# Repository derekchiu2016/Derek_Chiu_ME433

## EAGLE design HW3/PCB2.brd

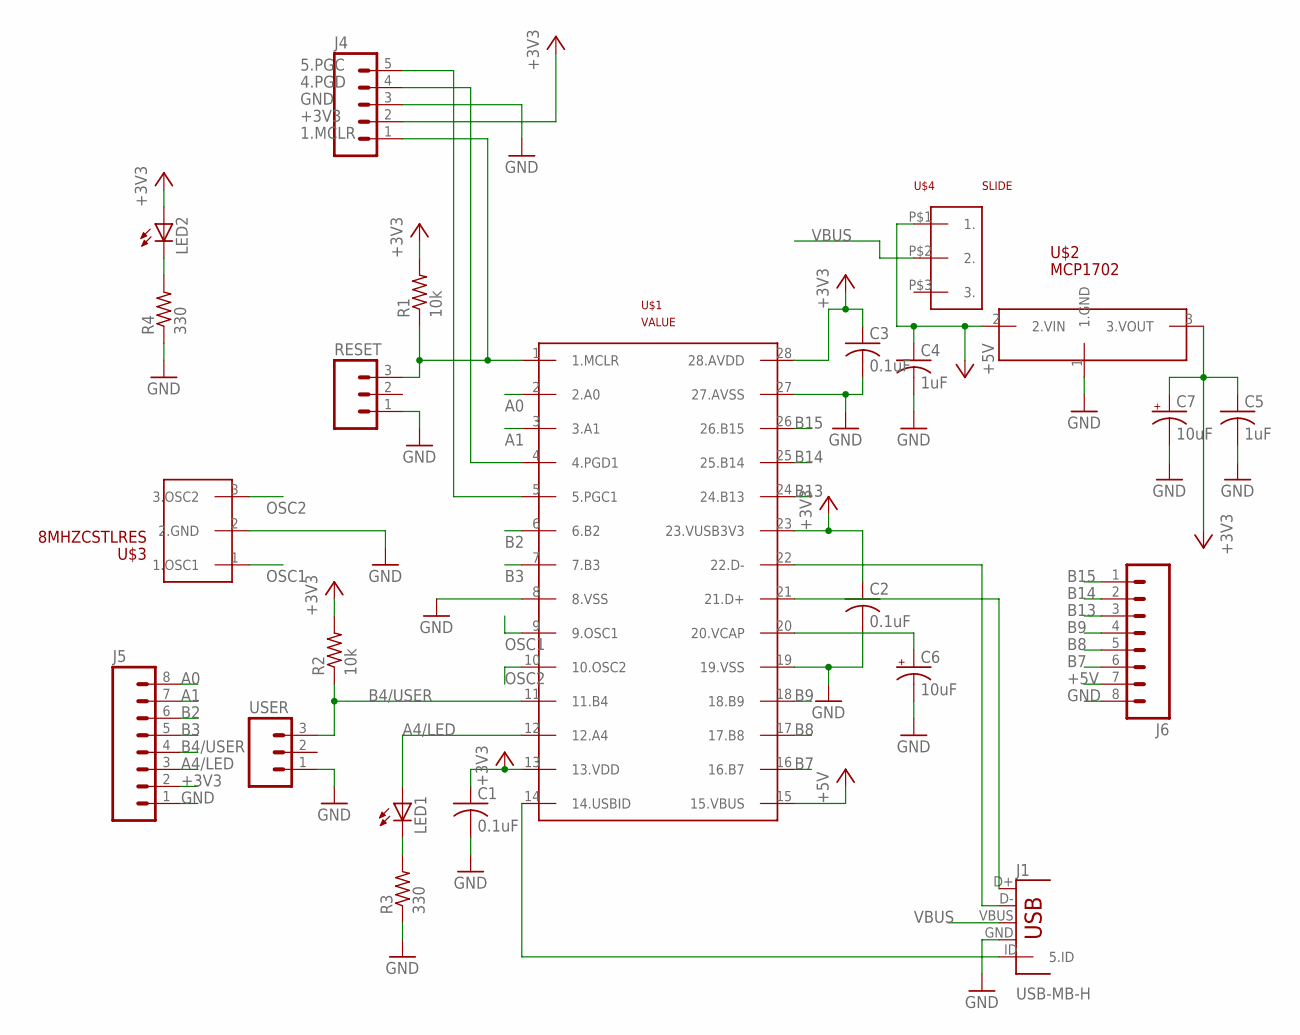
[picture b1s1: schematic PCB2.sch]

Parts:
C1, C2, C3: 0.1uF; C025-024X044
C4, C5: 1uF; C050-024X044
C6, C7: 10uF; TAP5-50
J1: USB-MB-H
J4: M05PTH; 1X05
J5, J6: M08; 1X08_ROUND
LED1, LED2: LED3MM
R1, R2: 10k; 0207/10
R3, R4: 330; 0207/10
RESET: M03PTH; 1X03
U$1: PIC32MX250F128B; DIL28-3
U$2: MCP1702; TO92
U$3: 8MHZCSTLRES; 1X03
U$4: SLIDE
USER: M03PTH; 1X03

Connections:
1.MCLR: J4.1, R1.1, RESET.3, U$1.1 (1.MCLR)
4.PGD: J4.4, U$1.4 (4.PGD1)
5.PGC: J4.5, U$1.5 (5.PGC1)
+3V3: C1.1, C2.1, C3.1, C5.1, C7.+, J4.2, J5.2, LED2.A, R1.2, R2.2, U$1.13 (13.VDD), U$1.23 (23.VUSB3V3), U$1.28 (28.AVDD), U$2.3 (3.VOUT)
+5V: C4.1, J6.7, U$1.15 (15.VBUS), U$2.2 (2.VIN), U$4.P$1 (1.)
A0: J5.8, U$1.2 (2.A0)
A1: J5.7, U$1.3 (3.A1)
A4/LED: J5.3, LED1.A, U$1.12 (12.A4)
B2: J5.6, U$1.6 (6.B2)
B3: J5.5, U$1.7 (7.B3)
B4/USER: J5.4, R2.1, U$1.11 (11.B4), USER.3
B7: J6.6, U$1.16 (16.B7)
B8: J6.5, U$1.17 (17.B8)
B9: J6.4, U$1.18 (18.B9)
B13: J6.3, U$1.24 (24.B13)
B14: J6.2, U$1.25 (25.B14)
B15: J6.1, U$1.26 (26.B15)
GND: C1.2, C2.2, C3.2, C4.2, C5.2, C6.-, C7.-, J1.GND, J4.3, J5.1, J6.8, R3.1, R4.1, RESET.1, U$1.8 (8.VSS), U$1.19 (19.VSS), U$1.27 (27.AVSS), U$2.1 (1.GND), U$3.2 (2.GND), USER.1
unnamed: LED1.K (C), R3.2
unnamed: J1.ID (5.ID), U$1.14 (14.USBID)
unnamed: J1.D-, U$1.22 (22.D-)
unnamed: J1.D+, U$1.21 (21.D+)
unnamed: C6.+, U$1.20 (20.VCAP)
unnamed: LED2.K (C), R4.2
OSC1: U$1.9 (9.OSC1), U$3.1 (1.OSC1)
OSC2: U$1.10 (10.OSC2), U$3.3 (3.OSC2)
VBUS: J1.VBUS, U$4.P$2 (2.)

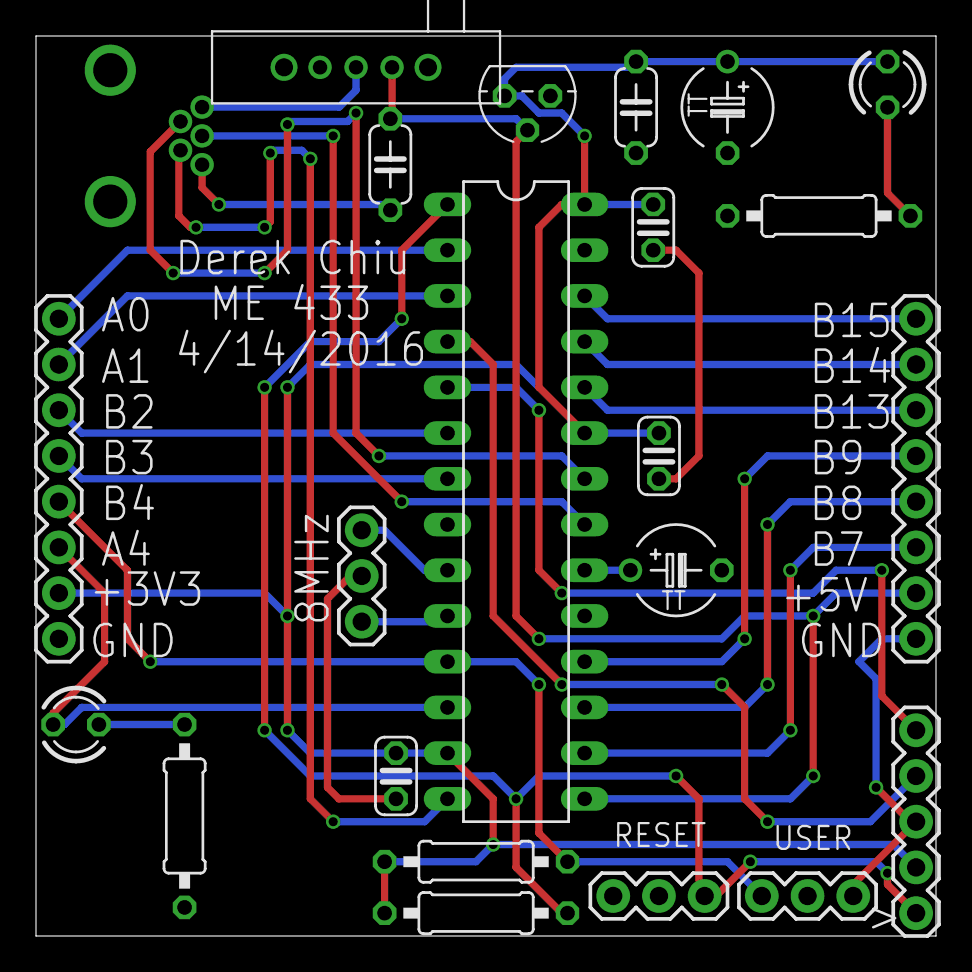
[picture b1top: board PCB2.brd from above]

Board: 2 copper layers, 50.0 x 50.0 mm, 23 parts (0 on the bottom side), 27 nets.

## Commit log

2016-03-31 :confetti_ball: Added .gitattributes & .gitignore files
2016-03-31 My first commit!
2016-03-31 Extra line added to change something
2016-04-02 Circuit pics, 3.3V oscill SShot, DEVCFG pragmas
    Added 2 pics of circuit
    Added screenshot of 3.3V oscillations due to no capacitors
    First edit of code filling out all DEVCFG registers
2016-04-04 Created new HW1 folder, same code
2016-04-04 PICkit3 working, initialized RB4 and RA4, LED from RA4 now ON
2016-04-04 Make LED turn ON/OFF every 5ms
    Using:
    _CP0_SET_COUNT
    _CP0_GET_COUNT
    LATAbits.LATA4
2016-04-04 Added code that turns off LED when pushbutton is pushed
    Using
    PORTBbits.RB4 to read pushbutton
    LATAbits.LATA4
2016-04-13 PCB Files
    Ready to be checked before order.
    NOTE: For some reason Eagle decided to lock my .sch and .brd files. Not
    exactly sure what it does, but just a heads up.
2016-04-13 Deleted HW2 folder
2016-04-16 Starting homework 4 code
    Copy and pasted sample SPI code from git
2016-04-16 For SPI: Added pin functions, added spi_io to setVoltage function
    Still need to figure out where pin functions go in the code.
    Still need to figure out how to fill out the rest of the DAC bits
2016-04-18 Finished setting up the spi_io function
    spi_io function now takes channel and voltage inputs and sends it to the
    SPI
    Next need to create the loops for the sine and triangle wave values
2016-04-18 setVoltage function complete
    Need to initiate and implement loops for sine wave and triangle wave
2016-04-19 Created sine and triangle waves
    Note: waves do not run exactly at 10 Hz
    Finished SPI DAC, time to start on I2C
2016-04-20 Copy and pasted i2c functions and changed all i2c1 to i2c2
2016-04-20 Set up initExpander, setExpander, and getExpander functions
    Next, need to incorporate inputs of setExpander into actual function
2016-04-20 Finished I2C initialization, need to work on set and getExpander functions
2016-04-21 Almost done, need to fix getExpander
2016-04-21 End HW4
    But double check getExpander function
2016-04-21 Fixed getExpander and finally added function prototypes
    problem was change char getExpander from void getExpander
2016-04-23 Create HW6, make sure IMU connections and I2C code works using WHOAMI reg
2016-04-23 Initialized IMU (3 registers), still missing some
    Initialized Accel, Gyro, and multi-read, but need to fill in some bits
    (x filter, etc.)
2016-04-23 Started i2c_read_multiple function
    Next, need to make sure addresses and stuff work
2016-04-24 Started PWM setup
    Need to correct the frequency, next need to change duty cycle depending
    on accelerations
2016-04-25 Finished setup of PWM
    f = 10kHz, duty cycle = 50%
2016-04-25 Solved i2c_read_multiple, set up 50Hz reading frequency
    Need to POWER CYCLE each time you upload code
2016-04-25 Set the sampling frequency to 50Hz and scale duty cycles depending on a_X and a_Y
2016-04-25 Minor edit
2016-05-06 Started HW5 (moving in all functions and library)
    Also contains minor edits to IMU hw/IMU tests
2016-05-06 completed drawCharacter function
    writes a single character at some coordinate
2016-05-06 uses LCD_drawArray to print Hello World! 1337
2016-05-07 Added pictures of Hello World 1337 and IMU reading
2016-05-13 Got IMU working
    Also uploaded new picture
2016-05-13 Added comments
2016-05-15 Android Hello World App
2016-05-30 Added laser cut box stuff
2016-05-31 Added more HWs
    Wheel, Camera App
2016-06-01 Added USB mouse
2016-06-02 Added CDC
2016-06-02 Updated camera app
2016-06-07 Finished racer PIC code, merged android CDC-cam
